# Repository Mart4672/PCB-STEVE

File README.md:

# PCB-STEVE
STM32F4 based Flight Computer Development PCB

STEVE, the name of this flight computer, is an acronym:
*Starter Testbed for Evolving the Vehicle Electronics*

As the name implies, the intention of STEVE is to be a testbed circuitboard for proving out avionics functionality.
STEVE is very much a development board as this is the first STM32 PCB that I have designed.

Future versions of STEVE will have a focus on exapnding a flight vehicle's envelope 
(Starter Testbed for Expanding the Vehicle Envelope)

STEVE is intended to be used on a flight vehicle such as a model rocket but can also be used in static environments such as a ground test stand.

## STEVE Version 1.1.0 Hardware Features
- 70 x 70 mm, 6 layer board with all components on one side for ease of manufacturing
- 1 STM32F407 Microcontroller
    - (STM32F407VGT6 is the specific SKU being used)
    - 1024 KB (1MB) of internal flash memory
    - 192 (112+16+64) KB of system RAM
- Reset and Boot buttons
- USB-C input for programming the microcontroller
    - the GCT USB4105-GF-A connector is allegedly rated for 5A
    - also usable for power when not connected to the PSM board
- Terminal block for 5V regulated input
- Micro SD card
- Winbond W25Q 128 Mbit (16 MB) external flash storage
- 1 BMI270 Inertial Measurement Unit (IMU) connected over SPI
- 1 BMP390 Barometric Pressure Sensor connected over SPI
- A 2x5 1.27mm pitch debug header
- A 32.768 kHz Low Speed External Crystal Oscillator
- A 8 MHz High Speed External Crystal Oscillator
- A TI TLV1117 1A 3.3V Output Linear Regulator
- A dedicated telemetry modem connection
    - uses screwless terminal blocks or a JST-GH connector
        - (each JST-GH connection is rated for 1A and the RFD900 has a max draw of ~1A at 5V)
    - GND, 5V, and UART signals (RX and TX) are present
    - placed close to both the USB-C and Regulated 5V power inputs
- 2 JST-SH 4 pin connectors for I2C
    - allows for easy hardware development for I2C devices (load cells, GNSS, etc)
- 1 passive buzzer (passive buzzers allow for different beep noises)
- 4 standard LEDs
- 2 WS2812 (NeoPixel) Addressable LEDs
- Additional GPIO and bus pins broken out
    - SPI2 (also used for BMP390) pins
    - UART1 pins
    - 2 ADC (12-bit) capable pins
    - Uses screwless terminal blocks
- Connectors for PSM board signals (3 x 6 pin connectors)
    - Uses JST-GH connectors
    - Servo PWM signals (4)
    - Mosfet gate signals (5)
    - Mosfet continuity signals (5)
    - Battery #1 Voltage sense line

## Future Updates

### Future STEVE Updates
- use a 3.3V plane on layer 5 (some signals ok) if doing a 6 layer board with components on 1 side
- move the 5V components to the same area
- make the board smaller (60 x 60 mm)
- consider moving the complicated components (BMI, BMP, WS2812) to a separate board
    - probably a bad idea since creating a simple daughter board with Standard PCBA would cost at least (10 PCB + 30 PCBA + 25 shipping) = $65
    - using Economic PCBA only saves ~$25
- give serious consideration to creating a STEVE revision with the PSM circuitry on the same board
    - keep in mind that any board orders also have tarrifs, taxes, and shipping applied, which can easily double the initial PCB/PCBA cost
- use a PMOS mosfet for reverse polarity protection
- add an RJ45 connector to utilize the ethernet capabilities of the STM32F407 (this might be part of a completely different board design)

## Using/opening this project on a different machine

- open the project file in KiCad

On the top bar, the following thing needs to be updated based on the machine you are using:
- Preferences > Configure Paths
Add an enironment variable with a name of:
CURRENT_PROJ_DIR
The value of the enirnment variable should be:
your-repo-dir-path/PCB-STEVE/hardware

On the top bar, the following things should not need to be updated but both use the CURRENT_PROJ_DIR variable 
- Preferences > Manage Symbol Libraries > Project Specific Libraries (tab)
- Preferences > Manage Footprint Libraries > Project Specific Libraries (tab)

## PCB Ordering Notes

#### STEVE V1.1.0 
STEVE V1.1.0 is a 6 layer PCB that uses vias as small as 
0.3mm (hole size) / 0.45mm (overall via diameter)

On JLC's website, 6 layer boards use the "Advanced PCB/PCBA service".
This has different default options from the standard service

Nonstandard options chosen for the advanced PCB service:

- (optional) Specify Stackup > No requirement
- Mark on PCB = 2D barcode (Serial Number)
    - 2D barcode Only | QR Code | STEVE_V1-1-0_SN | Remove Unique Number | 0001 
        - 8*8mm (5x5 also ok) | Specify Position (No Requirement is ok too)

Advanced Options
- $0.71 Blank Box

PCB Assembly Options
A board with 6 or fewer layers and single sided assembly qualifies for 
JLC's Economic PCBA
https://jlcpcb.com/capabilities/pcb-assembly-capabilities
See the above link for Economic PCBA constraints such as
- only supporting green silkscreens
- only supporting the ENIG finish

STEVE 1.1.0 is a 70 x 70mm board; using Standard PCBA auotmatically sets the 
board size to at least 70x70mm for adding edge rails/fiducials.
"The board size would be modified to be 80*70mm for Standard PCBA due to adding two 5mm edge rails on the shorter sides"

Nonstandard PCBA options chosen:
- PCBA Qty = 2 (can choose 2+ based on component availibility)
- Edge Rails/Fiducials = Added by JLCPCB (default)
- Confirm Parts Placement = Yes

Advanced Options
- Photo Confirmation = Yes (Not available for Economic)
- Conformal Coating (+cleaning) = No (can choose yes for future boards)
    - Not available for Economic PCBA
- Packaging = ESD+Cardboard (Cardboard is ok too)
- Solder Paste = Sn96.5/Ag3.0/Cu0.5 (Do NOT use Bismuth/Bi solder)
- The "Bake Components" option is not available for Economic PCBA
    - Will need to use the Standard PCBA service or omit the WS2812 LEDs (C2761795) from being assembled since they are moisture sensitive
- The BMI270 and BMP390 also require Standard PCBA

"Note: The setup fee is $25 per assembly side for Standard PCBA."

Stencil Order Options
- No stencil being ordered
    - If boards with many small pitch components (ex: STM32) are going to be assembled, a reflow oven is strongly recommended
    - if a stencil is ordered, make sure to get it cut to size to save on shipping costs

## Other Notes
- Don't use special characters such as "µ" for part designators, footprints, or values as this can cause issues with processing the bom and positions (CPL) files.

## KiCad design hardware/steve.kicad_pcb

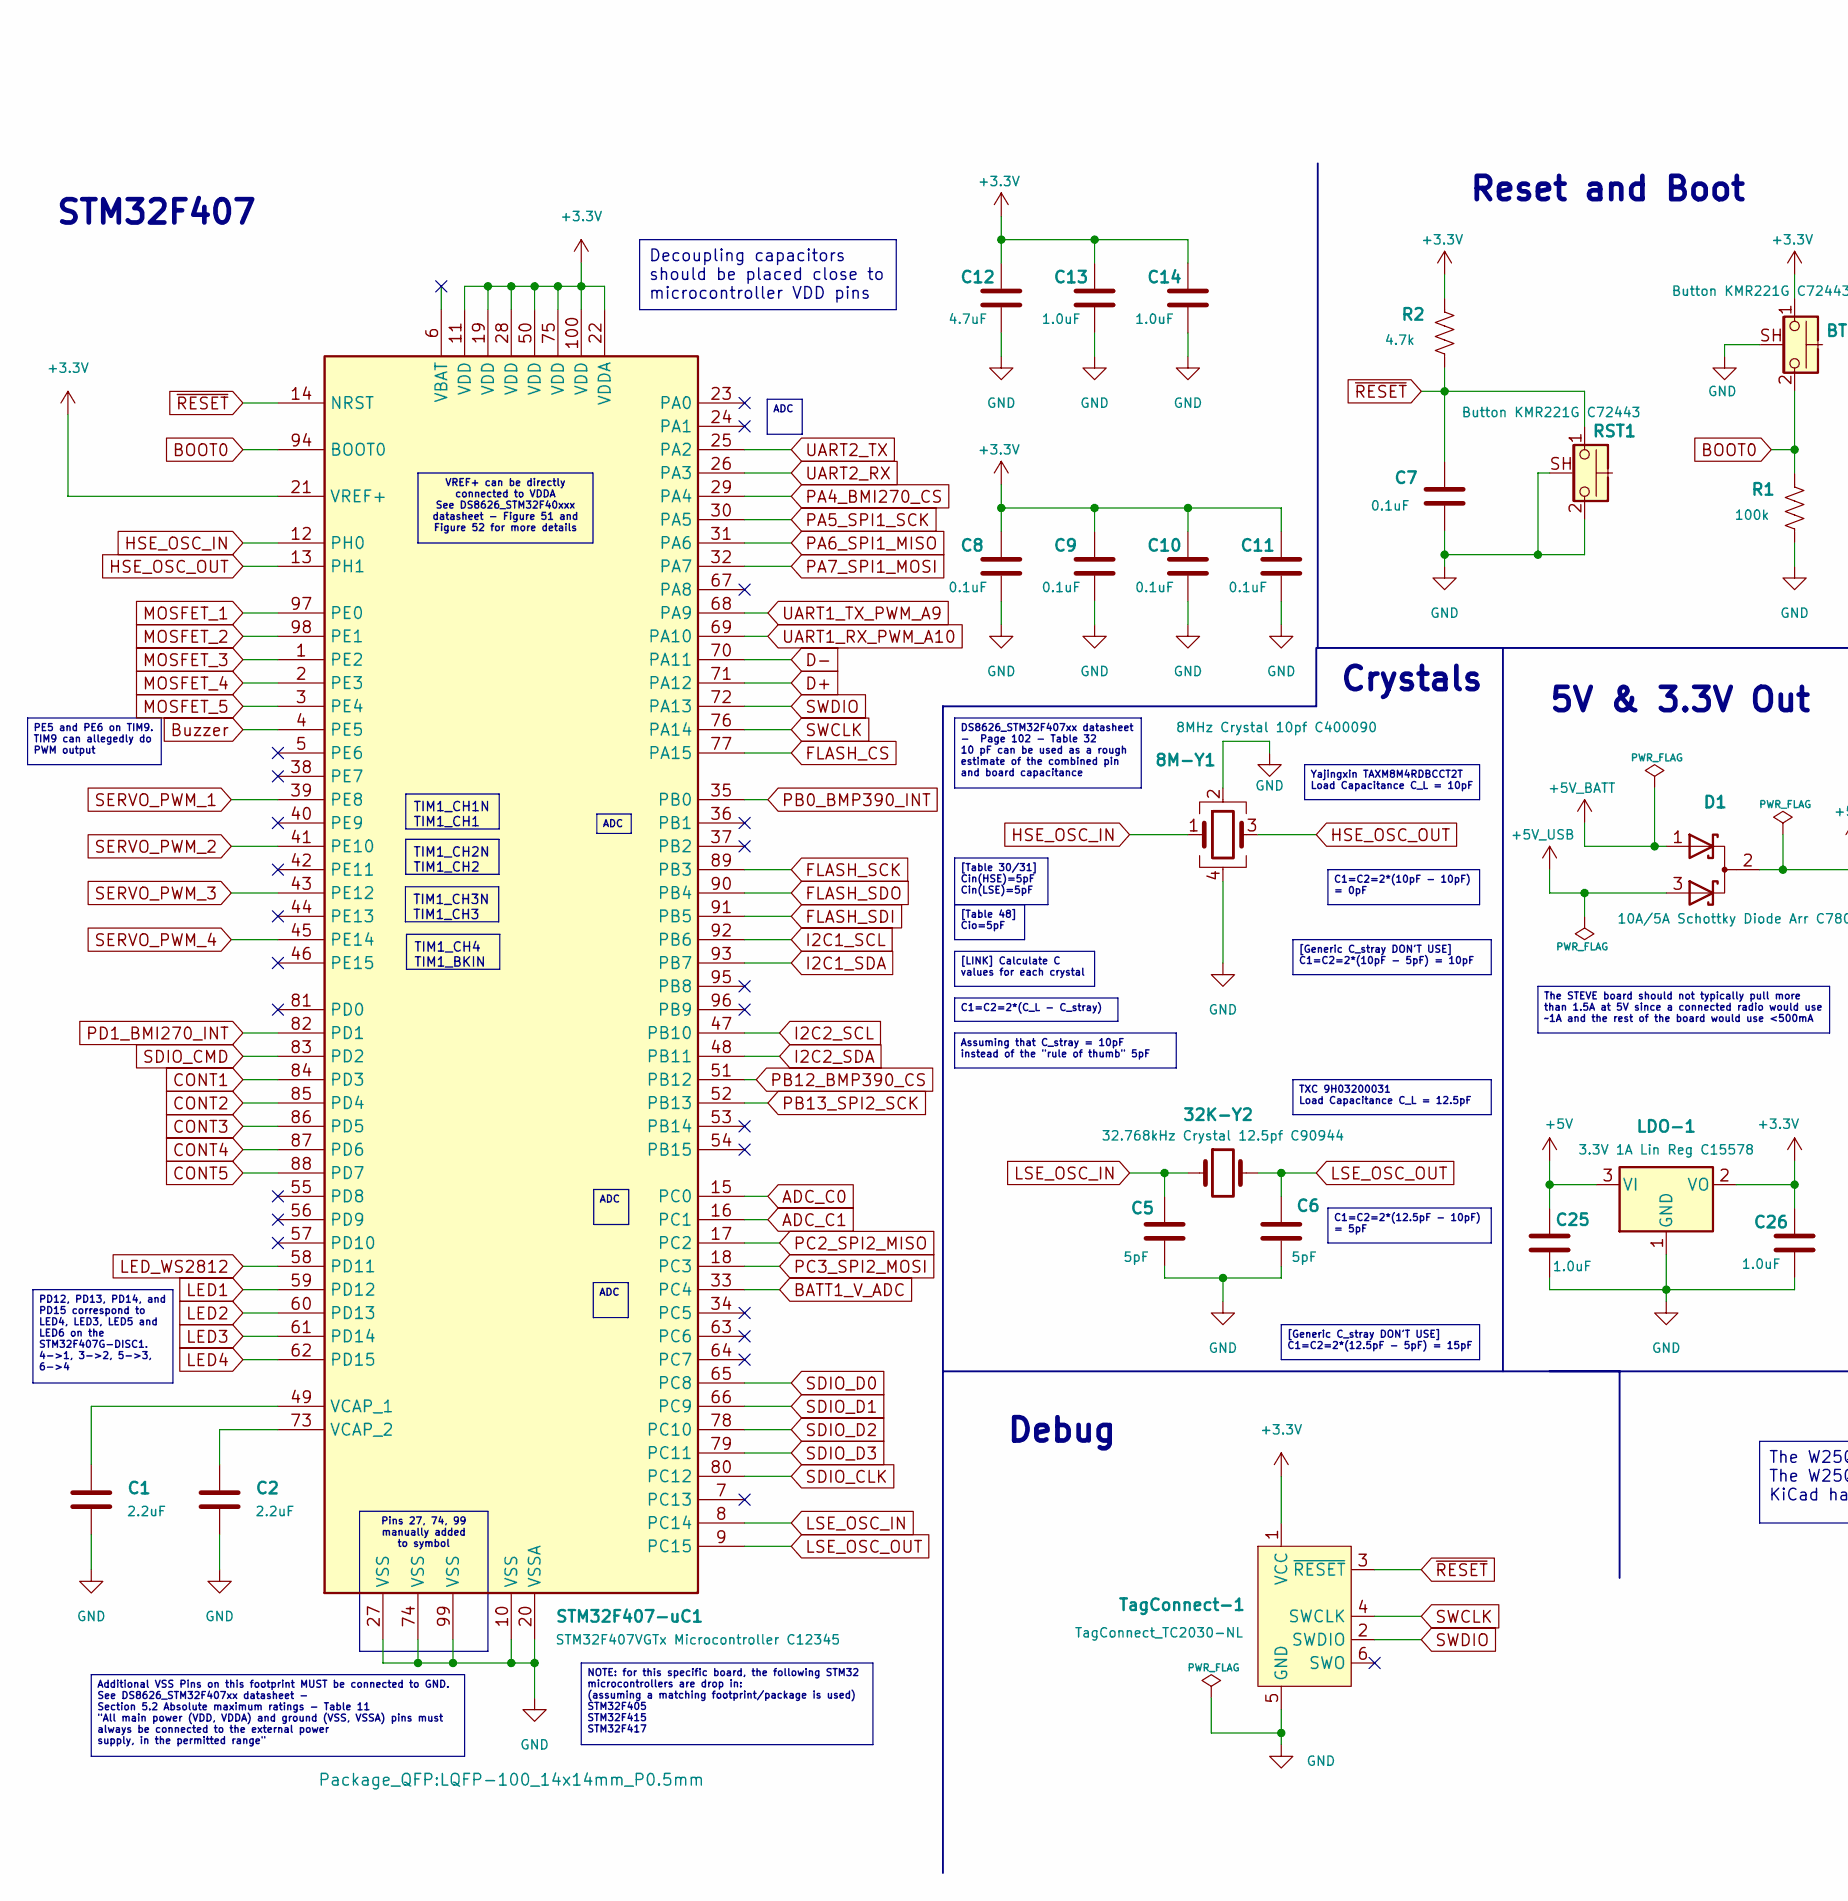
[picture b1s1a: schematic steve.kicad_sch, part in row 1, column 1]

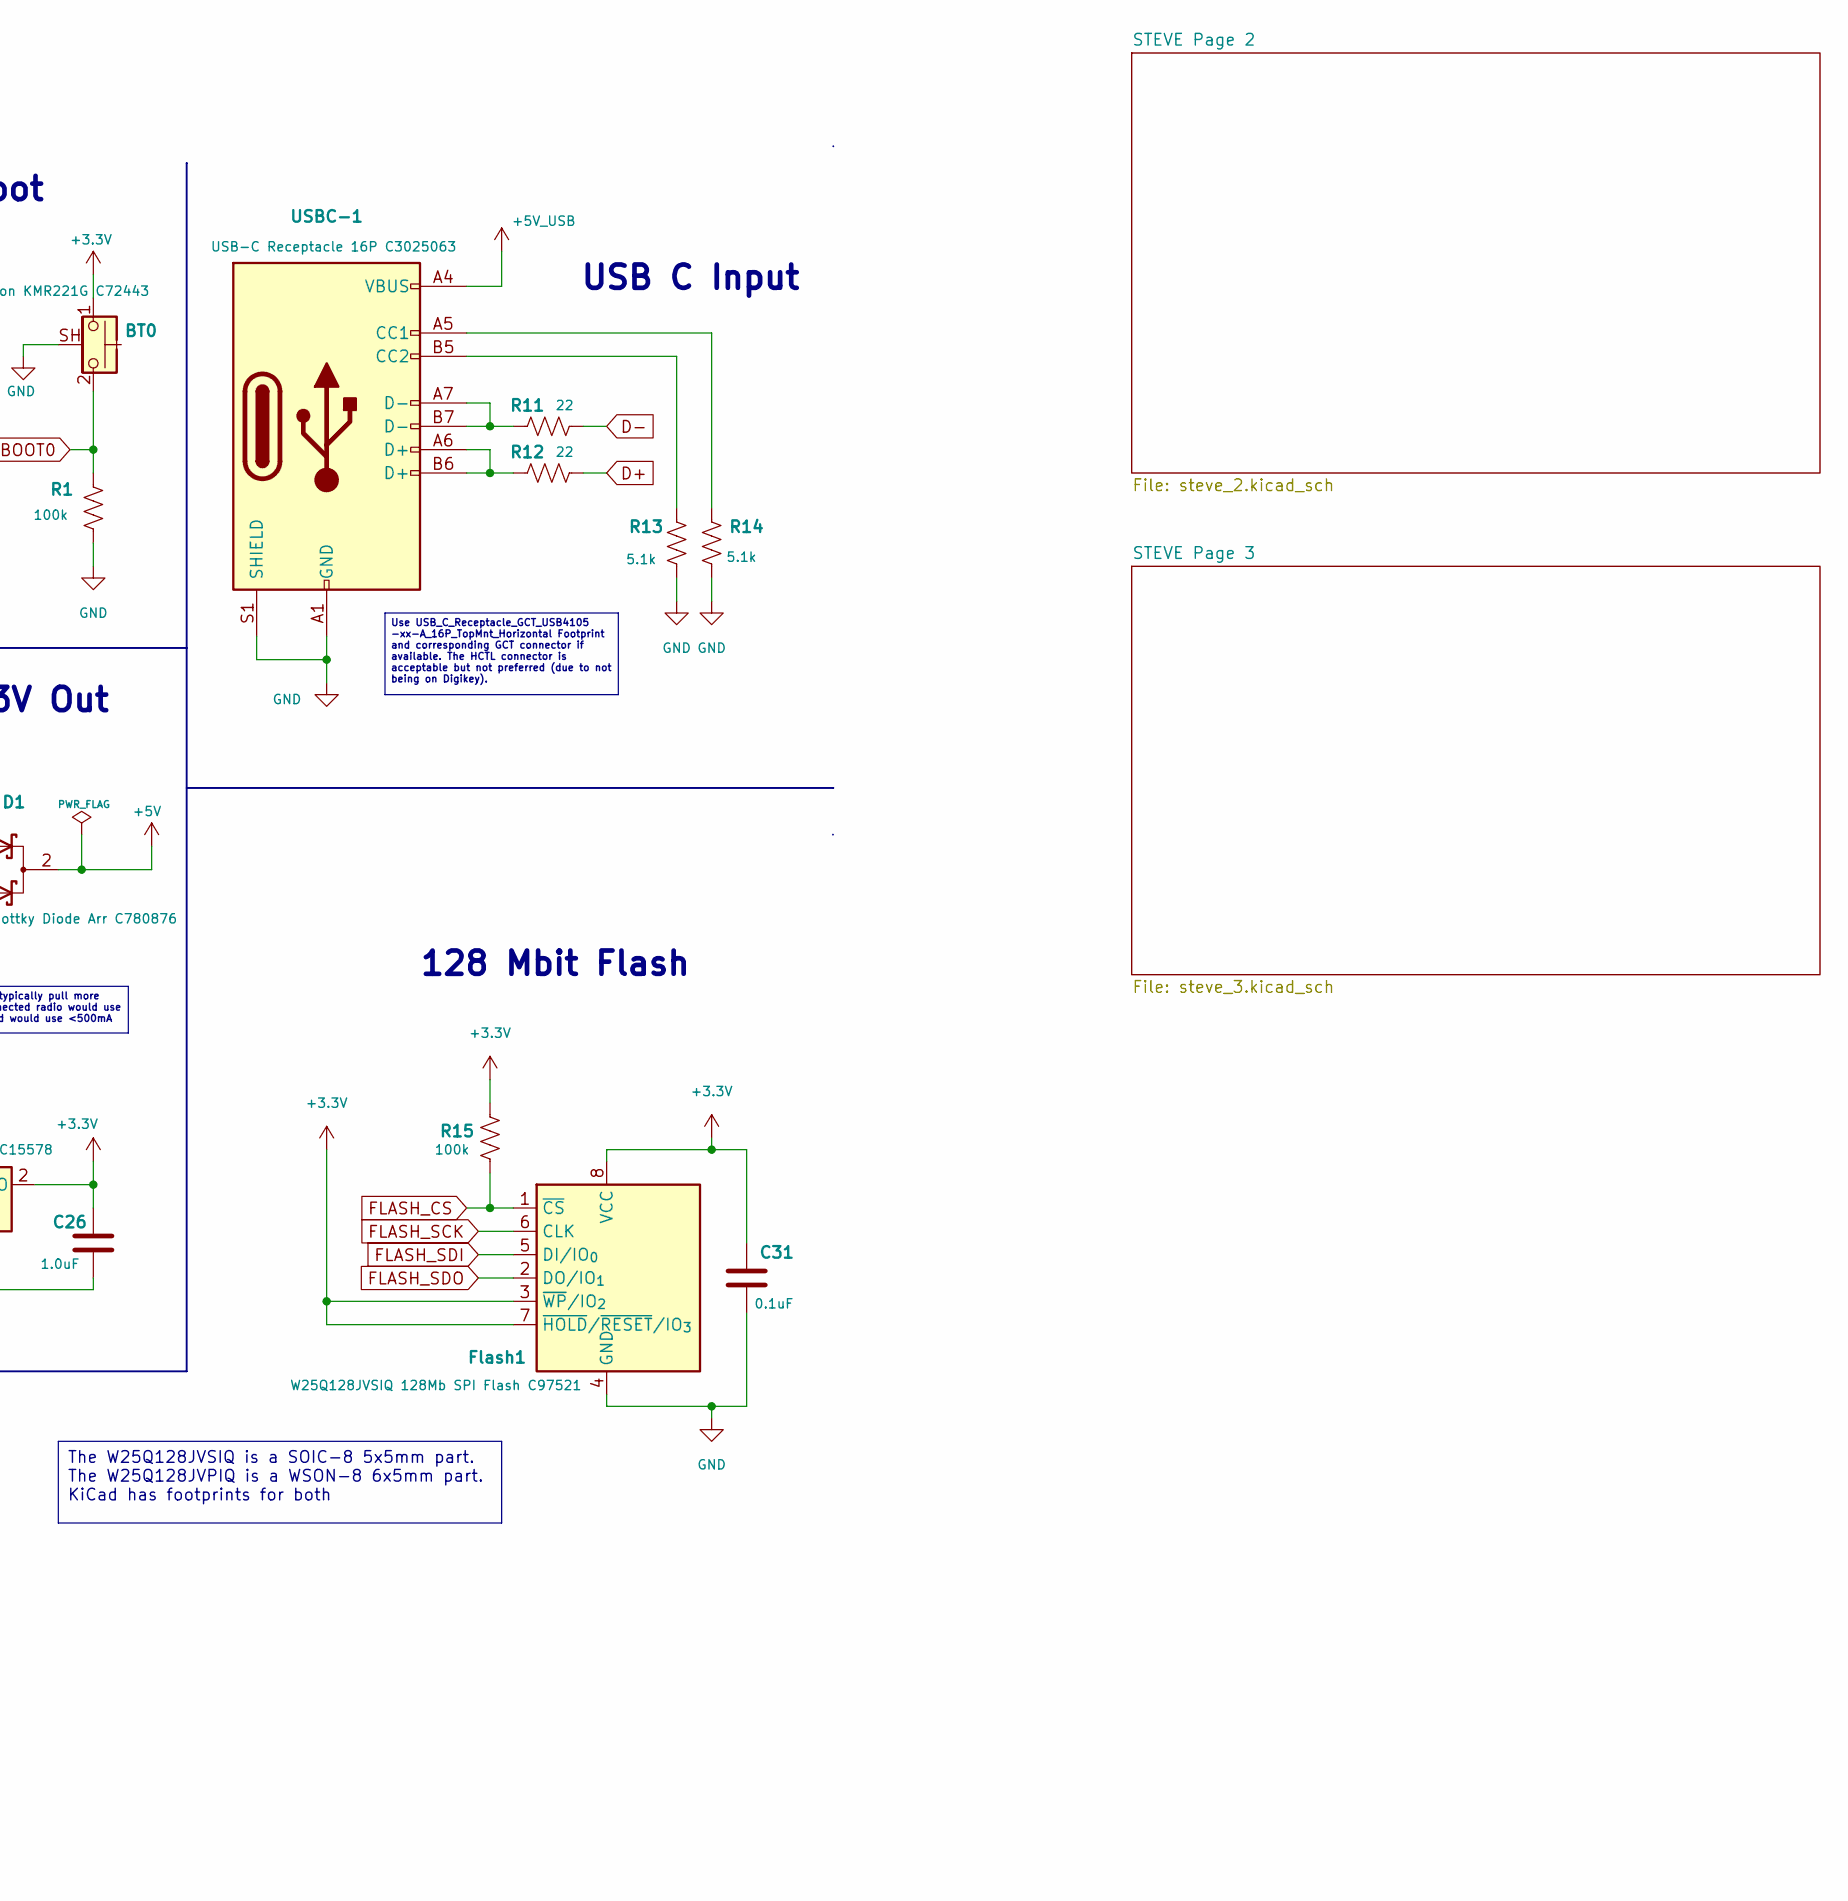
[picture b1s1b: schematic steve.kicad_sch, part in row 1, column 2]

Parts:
8M-Y1: 8MHz Crystal 10pf C400090; Crystal_SMD_3225-4Pin_3.2x2.5mm
32K-Y2: 32.768kHz Crystal 12.5pf C90944; Crystal_SMD_3215-2Pin_3.2x1.5mm
BT0: Button KMR221G C72443; SW_Push_3D_1P1T-SH_NO_CK_KMR2xxG
C1, C2: 2.2uF; C_0603_1608Metric
C5, C6: 5pF; C_0603_1608Metric
C7, C8, C9, C10, C11, C31: 0.1uF; C_0603_1608Metric
C12: 4.7uF; C_0603_1608Metric
C13, C14: 1.0uF; C_0603_1608Metric
C25, C26: 1.0uF; C_1206_3216Metric
D1: 10A/5A Schottky Diode Arr C780876; PDS1040CTL-13_PowerDI-5
Flash1: W25Q128JVSIQ 128Mb SPI Flash C97521; SOIC-8_5.23x5.23mm_P1.27mm_3D
LDO-1: 3.3V 1A Lin Reg C15578; SOT-223-3_TabPin2
R1, R15: 100k; R_0603_1608Metric
R2: 4.7k; R_0603_1608Metric
R11, R12: 22; R_0603_1608Metric
R13, R14: 5.1k; R_0603_1608Metric
RST1: Button KMR221G C72443; SW_Push_3D_1P1T-SH_NO_CK_KMR2xxG
STM32F407-uC1: STM32F407VGTx Microcontroller C12345; LQFP-100_14x14mm_P0.5mm
TagConnect-1: TagConnect_TC2030-NL; Tag-Connect_TC2030-IDC-NL_2x03_P1.27mm_Vertical
USBC-1: USB-C Receptacle 16P C3025063; USB_C_Receptacle_3D_HCTL_HC-TYPE-C-16P-01A

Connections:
+3.3V: BT0.1, C8.1, C9.1, C10.1, C11.1, C12.1, C13.1, C14.1, C26.1, C31.1, Flash1.3 (~WP/IO_{2}), Flash1.7 (~HOLD/~RESET/IO_{3}), Flash1.8 (VCC), LDO-1.2 (VO), R2.1, R15.1, STM32F407-uC1.11 (VDD), STM32F407-uC1.19 (VDD), STM32F407-uC1.21 (VREF+), STM32F407-uC1.22 (VDDA), STM32F407-uC1.28 (VDD), STM32F407-uC1.50 (VDD), STM32F407-uC1.75 (VDD), STM32F407-uC1.100 (VDD), TagConnect-1.1 (VCC); also elsewhere on the board
+5V: C25.1, D1.2 (K), LDO-1.3 (VI); also elsewhere on the board
+5V_BATT: D1.1 (A); also elsewhere on the board
+5V_USB: D1.3 (A), USBC-1.A4 (VBUS), USBC-1.A9 (VBUS), USBC-1.B4 (VBUS), USBC-1.B9 (VBUS)
ADC_C0: STM32F407-uC1.15 (PC0); also elsewhere on the board
ADC_C1: STM32F407-uC1.16 (PC1); also elsewhere on the board
BATT1_V_ADC: STM32F407-uC1.33 (PC4); also elsewhere on the board
BOOT0: BT0.2, R1.1, STM32F407-uC1.94 (BOOT0)
Buzzer: STM32F407-uC1.4 (PE5); also elsewhere on the board
CONT1: STM32F407-uC1.84 (PD3); also elsewhere on the board
CONT2: STM32F407-uC1.85 (PD4); also elsewhere on the board
CONT3: STM32F407-uC1.86 (PD5); also elsewhere on the board
CONT4: STM32F407-uC1.87 (PD6); also elsewhere on the board
CONT5: STM32F407-uC1.88 (PD7); also elsewhere on the board
D+: R12.2, STM32F407-uC1.71 (PA12)
D-: R11.2, STM32F407-uC1.70 (PA11)
FLASH_CS: Flash1.1 (~CS), R15.2, STM32F407-uC1.77 (PA15)
FLASH_SCK: Flash1.6 (CLK), STM32F407-uC1.89 (PB3)
FLASH_SDI: Flash1.5 (DI/IO_{0}), STM32F407-uC1.91 (PB5)
FLASH_SDO: Flash1.2 (DO/IO_{1}), STM32F407-uC1.90 (PB4)
GND: 8M-Y1.2, 8M-Y1.4, BT0.SH (B), C1.2, C2.2, C5.2, C6.2, C7.2, C8.2, C9.2, C10.2, C11.2, C12.2, C13.2, C14.2, C25.2, C26.2, C31.2, Flash1.4 (GND), LDO-1.1 (GND), R1.2, R13.2, R14.2, RST1.2, RST1.SH (B), STM32F407-uC1.10 (VSS), STM32F407-uC1.20 (VSSA), STM32F407-uC1.27 (VSS), STM32F407-uC1.74 (VSS), STM32F407-uC1.99 (VSS), TagConnect-1.5 (GND), USBC-1.A1 (GND), USBC-1.A12 (GND), USBC-1.B1 (GND), USBC-1.B12 (GND), USBC-1.S1 (SHIELD); also elsewhere on the board
HSE_OSC_IN: 8M-Y1.1, STM32F407-uC1.12 (PH0)
HSE_OSC_OUT: 8M-Y1.3, STM32F407-uC1.13 (PH1)
I2C1_SCL: STM32F407-uC1.92 (PB6); also elsewhere on the board
I2C1_SDA: STM32F407-uC1.93 (PB7); also elsewhere on the board
I2C2_SCL: STM32F407-uC1.47 (PB10); also elsewhere on the board
I2C2_SDA: STM32F407-uC1.48 (PB11); also elsewhere on the board
LED1: STM32F407-uC1.59 (PD12); also elsewhere on the board
LED2: STM32F407-uC1.60 (PD13); also elsewhere on the board
LED3: STM32F407-uC1.61 (PD14); also elsewhere on the board
LED4: STM32F407-uC1.62 (PD15); also elsewhere on the board
LED_WS2812: STM32F407-uC1.58 (PD11); also elsewhere on the board
LSE_OSC_IN: 32K-Y2.1, C5.1, STM32F407-uC1.8 (PC14)
LSE_OSC_OUT: 32K-Y2.2, C6.1, STM32F407-uC1.9 (PC15)
MOSFET_1: STM32F407-uC1.97 (PE0); also elsewhere on the board
MOSFET_2: STM32F407-uC1.98 (PE1); also elsewhere on the board
MOSFET_3: STM32F407-uC1.1 (PE2); also elsewhere on the board
MOSFET_4: STM32F407-uC1.2 (PE3); also elsewhere on the board
MOSFET_5: STM32F407-uC1.3 (PE4); also elsewhere on the board
unnamed: R11.1, USBC-1.A7 (D-), USBC-1.B7 (D-)
unnamed: R12.1, USBC-1.A6 (D+), USBC-1.B6 (D+)
unnamed: C1.1, STM32F407-uC1.49 (VCAP_1)
unnamed: C2.1, STM32F407-uC1.73 (VCAP_2)
unnamed: R14.1, USBC-1.A5 (CC1)
unnamed: R13.1, USBC-1.B5 (CC2)
PA4_BMI270_CS: STM32F407-uC1.29 (PA4); also elsewhere on the board
PA5_SPI1_SCK: STM32F407-uC1.30 (PA5); also elsewhere on the board
PA6_SPI1_MISO: STM32F407-uC1.31 (PA6); also elsewhere on the board
PA7_SPI1_MOSI: STM32F407-uC1.32 (PA7); also elsewhere on the board
PB0_BMP390_INT: STM32F407-uC1.35 (PB0); also elsewhere on the board
PB12_BMP390_CS: STM32F407-uC1.51 (PB12); also elsewhere on the board
PB13_SPI2_SCK: STM32F407-uC1.52 (PB13); also elsewhere on the board
PC2_SPI2_MISO: STM32F407-uC1.17 (PC2); also elsewhere on the board
PC3_SPI2_MOSI: STM32F407-uC1.18 (PC3); also elsewhere on the board
PD1_BMI270_INT: STM32F407-uC1.82 (PD1); also elsewhere on the board
SDIO_CLK: STM32F407-uC1.80 (PC12); also elsewhere on the board
SDIO_CMD: STM32F407-uC1.83 (PD2); also elsewhere on the board
SDIO_D0: STM32F407-uC1.65 (PC8); also elsewhere on the board
SDIO_D1: STM32F407-uC1.66 (PC9); also elsewhere on the board
SDIO_D2: STM32F407-uC1.78 (PC10); also elsewhere on the board
SDIO_D3: STM32F407-uC1.79 (PC11); also elsewhere on the board
SERVO_PWM_1: STM32F407-uC1.39 (PE8); also elsewhere on the board
SERVO_PWM_2: STM32F407-uC1.41 (PE10); also elsewhere on the board
SERVO_PWM_3: STM32F407-uC1.43 (PE12); also elsewhere on the board
SERVO_PWM_4: STM32F407-uC1.45 (PE14); also elsewhere on the board
SWCLK: STM32F407-uC1.76 (PA14), TagConnect-1.4 (SWCLK)
SWDIO: STM32F407-uC1.72 (PA13), TagConnect-1.2 (SWDIO)
UART1_RX_PWM_A10: STM32F407-uC1.69 (PA10); also elsewhere on the board
UART1_TX_PWM_A9: STM32F407-uC1.68 (PA9); also elsewhere on the board
UART2_RX: STM32F407-uC1.26 (PA3); also elsewhere on the board
UART2_TX: STM32F407-uC1.25 (PA2); also elsewhere on the board
~RESET: C7.1, R2.2, RST1.1, STM32F407-uC1.14 (NRST), TagConnect-1.3 (~RESET)

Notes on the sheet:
128 Mbit Flash
5V & 3.3V Out
STM32F407
Debug
USB C Input
Reset and Boot
Crystals
TXC 9H03200031 Load Capacitance C_L = 12.5pF
TIM1_CH4 TIM1_BKIN
C1=C2=2*(12.5pF - 10pF) = 5pF
The STEVE board should not typically pull more than 1.5A at 5V since a connected radio would use ~1A and the rest of the board would use <500mA
The W25Q128JVSIQ is a SOIC-8 5x5mm part. The W25Q128JVPIQ is a WSON-8 6x5mm part. KiCad has footprints for both
ADC
C1=C2=2*(C_L - C_stray)
NOTE: for this specific board, the following STM32 microcontrollers are drop in: (assuming a matching footprint/package is used) STM32F405 STM32F415 STM32F417
VREF+ can be directly connected to VDDA See DS8626_STM32F40xxx datasheet - Figure 51 and Figure 52 for more details
PD12, PD13, PD14, and PD15 correspond to LED4, LED3, LED5 and LED6 on the STM32F407G-DISC1. 4->1, 3->2, 5->3, 6->4
Assuming that C_stray = 10pF instead of the "rule of thumb" 5pF
TIM1_CH3N TIM1_CH3
TIM1_CH1N TIM1_CH1
Additional VSS Pins on this footprint MUST be connected to GND. See DS8626_STM32F407xx datasheet - Section 5.2 Absolute maximum ratings - Table 11 "All main power (VDD, VDDA) and ground (VSS, VSSA) pins must always be connected to the external power supply, in the permitted range"
[Generic C_stray DON'T USE] C1=C2=2*(12.5pF - 5pF) = 15pF
C1=C2=2*(10pF - 10pF) = 0pF
[Table 48] Cio=5pF
Pins 27, 74, 99 manually added to symbol
Yajingxin TAXM8M4RDBCCT2T Load Capacitance C_L = 10pF
Use USB_C_Receptacle_GCT_USB4105 -xx-A_16P_TopMnt_Horizontal Footprint and corresponding GCT connector if available. The HCTL connector is acceptable but not preferred (due to not being on Digikey).
Decoupling capacitors should be placed close to microcontroller VDD pins
[Generic C_stray DON'T USE] C1=C2=2*(10pF - 5pF) = 10pF
PE5 and PE6 on TIM9. TIM9 can allegedly do PWM output
DS8626_STM32F407xx datasheet - Page 102 - Table 32 10 pF can be used as a rough estimate of the combined pin and board capacitance
[Table 30/31] Cin(HSE)=5pF Cin(LSE)=5pF
[LINK] Calculate C values for each crystal
TIM1_CH2N TIM1_CH2

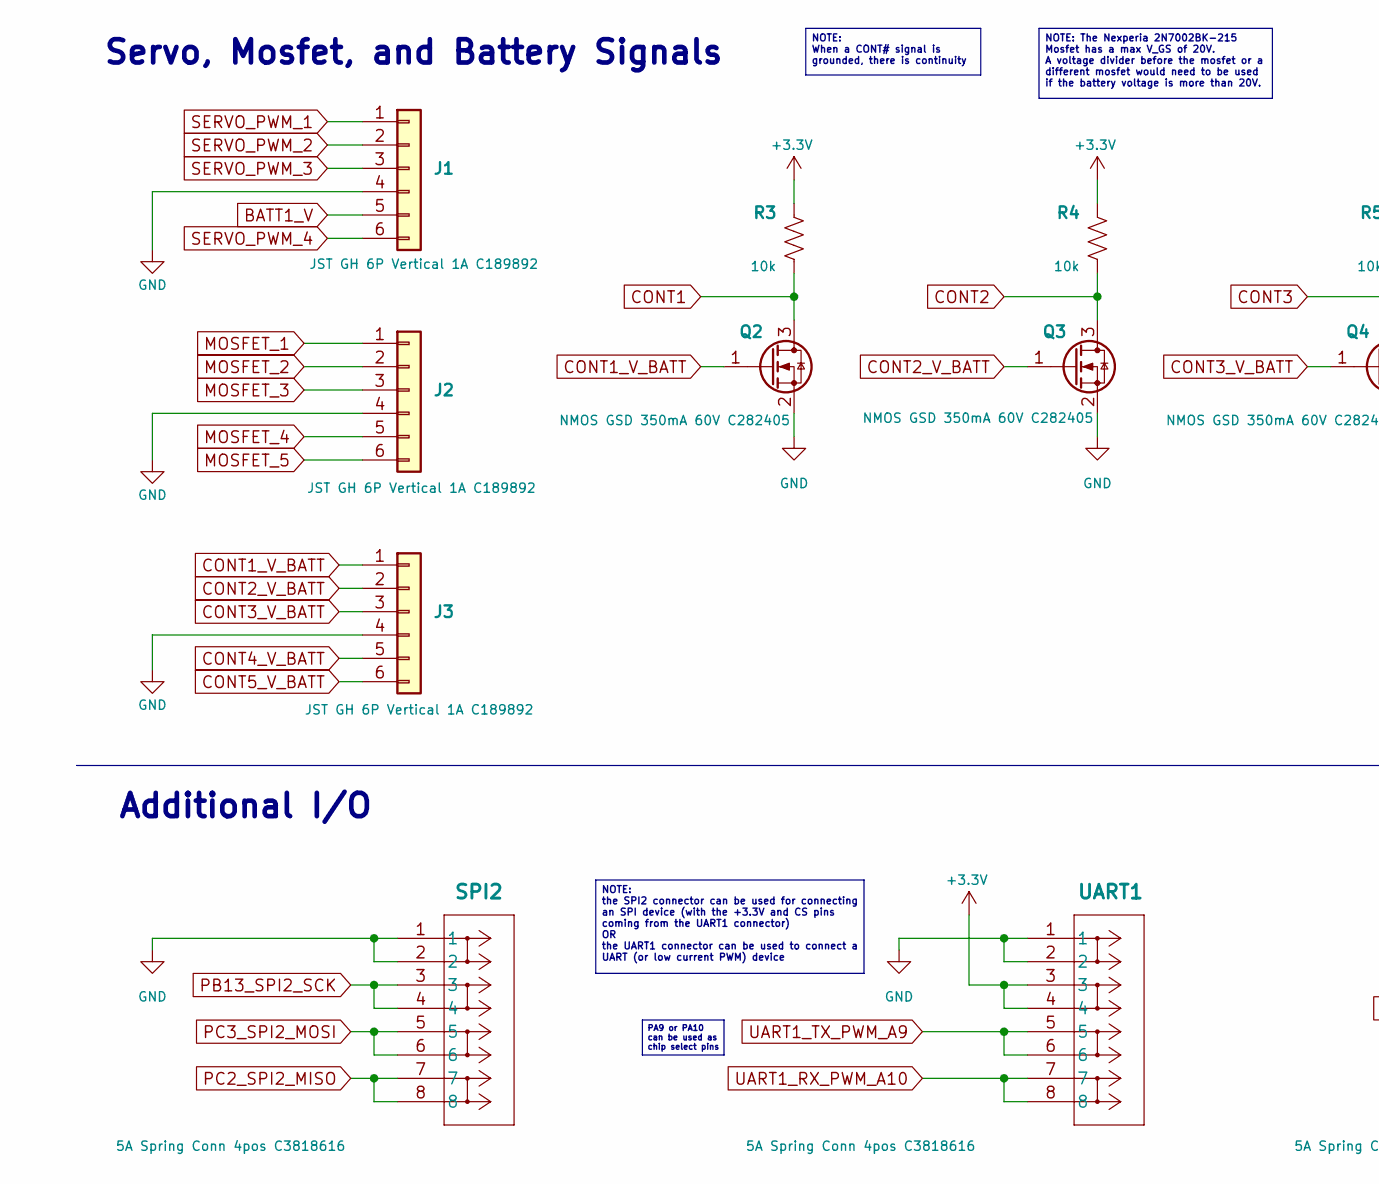
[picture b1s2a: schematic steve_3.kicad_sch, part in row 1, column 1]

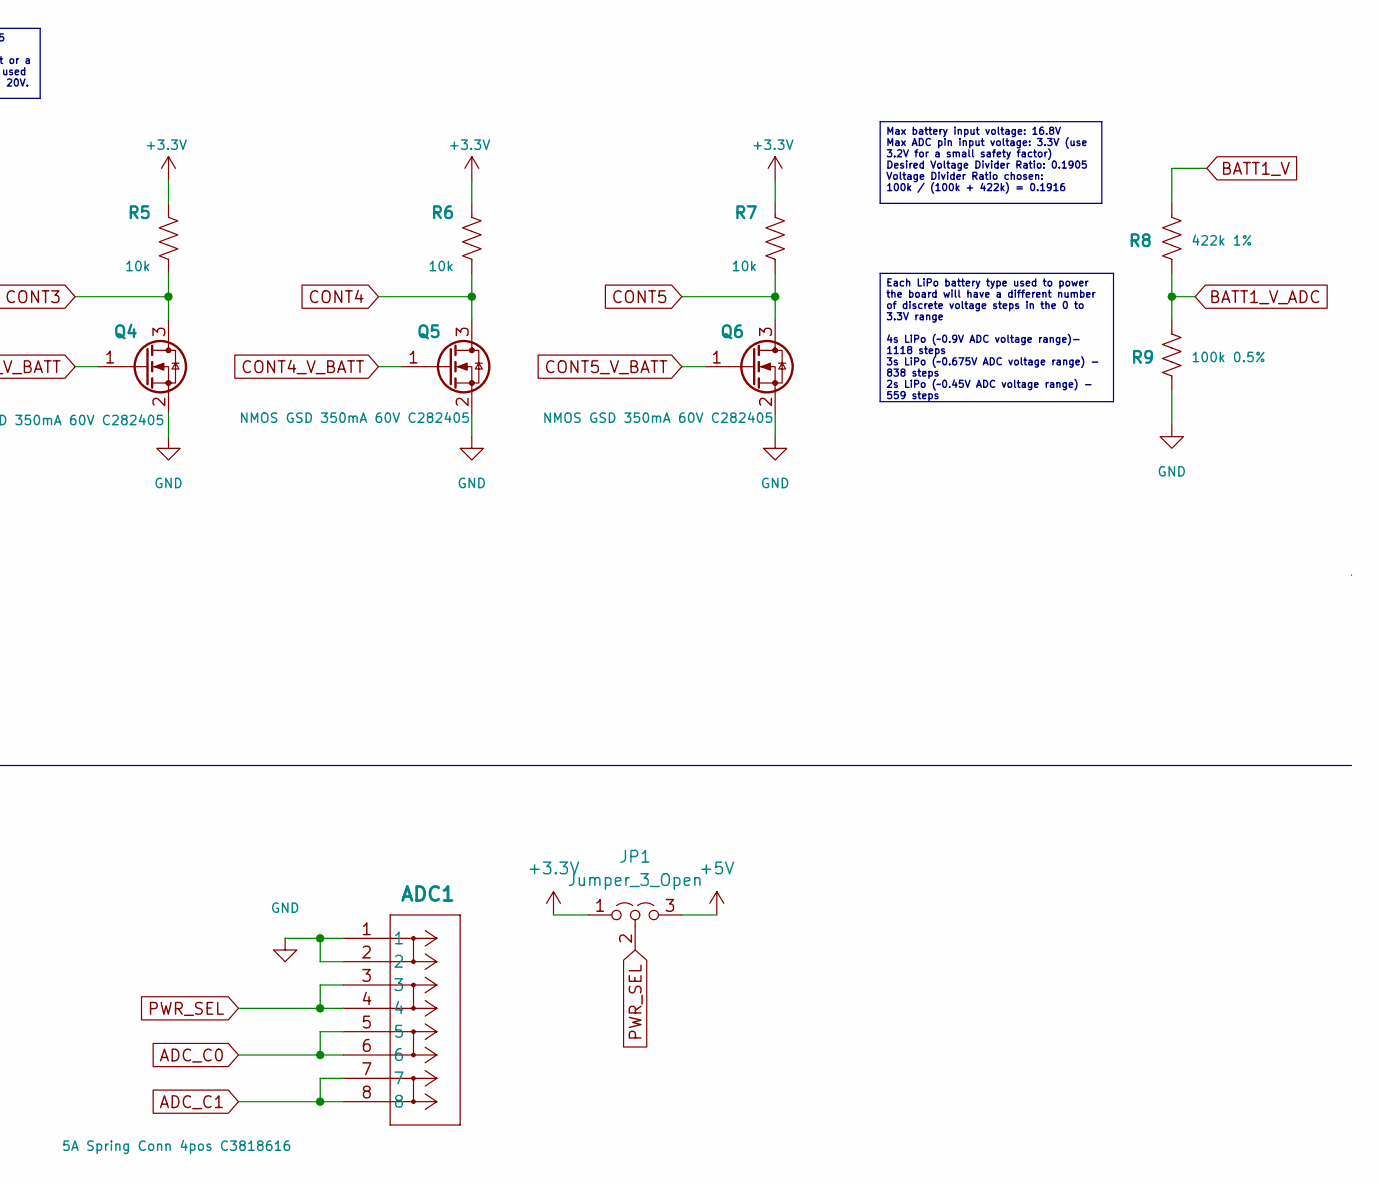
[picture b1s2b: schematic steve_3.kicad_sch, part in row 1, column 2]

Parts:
ADC1: 5A Spring Conn 4pos C3818616; CONN_1814582_TerminalBlock_1770979_4pos_Vertical
J1, J2, J3: JST GH 6P Vertical 1A C189892; JST_GH_BM06B-GHS-TBT_1x06-1MP_P1.25mm_Vertical
JP1: Jumper_3_Open; PinHeader_1x03_P1.27mm_Vertical
Q2, Q3, Q4, Q5, Q6: NMOS GSD 350mA 60V C282405; SOT-23
R3, R4, R5, R6, R7: 10k; R_0603_1608Metric
R8: 422k 1%; R_0603_1608Metric
R9: 100k 0.5%; R_0603_1608Metric
SPI2: 5A Spring Conn 4pos C3818616; CONN_1814582_TerminalBlock_1770979_4pos_Vertical
UART1: 5A Spring Conn 4pos C3818616; CONN_1814582_TerminalBlock_1770979_4pos_Vertical

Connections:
+3.3V: JP1.1 (A), R3.2, R4.2, R5.2, R6.2, R7.2, UART1.3, UART1.4; also elsewhere on the board
+5V: JP1.3 (B); also elsewhere on the board
ADC_C0: ADC1.5, ADC1.6; also elsewhere on the board
ADC_C1: ADC1.7, ADC1.8; also elsewhere on the board
BATT1_V: J1.5, R8.2
BATT1_V_ADC: R8.1, R9.2; also elsewhere on the board
CONT1: Q2.3 (D), R3.1; also elsewhere on the board
CONT1_V_BATT: J3.1, Q2.1 (G)
CONT2: Q3.3 (D), R4.1; also elsewhere on the board
CONT2_V_BATT: J3.2, Q3.1 (G)
CONT3: Q4.3 (D), R5.1; also elsewhere on the board
CONT3_V_BATT: J3.3, Q4.1 (G)
CONT4: Q5.3 (D), R6.1; also elsewhere on the board
CONT4_V_BATT: J3.5, Q5.1 (G)
CONT5: Q6.3 (D), R7.1; also elsewhere on the board
CONT5_V_BATT: J3.6, Q6.1 (G)
GND: ADC1.1, ADC1.2, J1.4, J2.4, J3.4, Q2.2 (S), Q3.2 (S), Q4.2 (S), Q5.2 (S), Q6.2 (S), R9.1, SPI2.1, SPI2.2, UART1.1, UART1.2; also elsewhere on the board
MOSFET_1: J2.1; also elsewhere on the board
MOSFET_2: J2.2; also elsewhere on the board
MOSFET_3: J2.3; also elsewhere on the board
MOSFET_4: J2.5; also elsewhere on the board
MOSFET_5: J2.6; also elsewhere on the board
PB13_SPI2_SCK: SPI2.3, SPI2.4; also elsewhere on the board
PC2_SPI2_MISO: SPI2.7, SPI2.8; also elsewhere on the board
PC3_SPI2_MOSI: SPI2.5, SPI2.6; also elsewhere on the board
PWR_SEL: ADC1.3, ADC1.4, JP1.2 (C)
SERVO_PWM_1: J1.1; also elsewhere on the board
SERVO_PWM_2: J1.2; also elsewhere on the board
SERVO_PWM_3: J1.3; also elsewhere on the board
SERVO_PWM_4: J1.6; also elsewhere on the board
UART1_RX_PWM_A10: UART1.7, UART1.8; also elsewhere on the board
UART1_TX_PWM_A9: UART1.5, UART1.6; also elsewhere on the board

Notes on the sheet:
Servo, Mosfet, and Battery Signals
Additional I/O
NOTE: the SPI2 connector can be used for connecting an SPI device (with the +3.3V and CS pins coming from the UART1 connector) OR the UART1 connector can be used to connect a UART (or low current PWM) device
NOTE: When a CONT# signal is grounded, there is continuity
PA9 or PA10 can be used as chip select pins
Max battery input voltage: 16.8V Max ADC pin input voltage: 3.3V (use 3.2V for a small safety factor) Desired Voltage Divider Ratio: 0.1905 Voltage Divider Ratio chosen: 100k / (100k + 422k) = 0.1916
NOTE: The Nexperia 2N7002BK-215 Mosfet has a max V_GS of 20V. A voltage divider before the mosfet or a different mosfet would need to be used if the battery voltage is more than 20V.
Each LiPo battery type used to power the board will have a different number of discrete voltage steps in the 0 to 3.3V range 4s LiPo (~0.9V ADC voltage range)- 1118 steps 3s LiPo (~0.675V ADC voltage range) - 838 steps 2s LiPo (~0.45V ADC voltage range) - 559 steps
